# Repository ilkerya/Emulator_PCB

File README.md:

Emulator Hardware
Designed in Kicad 9

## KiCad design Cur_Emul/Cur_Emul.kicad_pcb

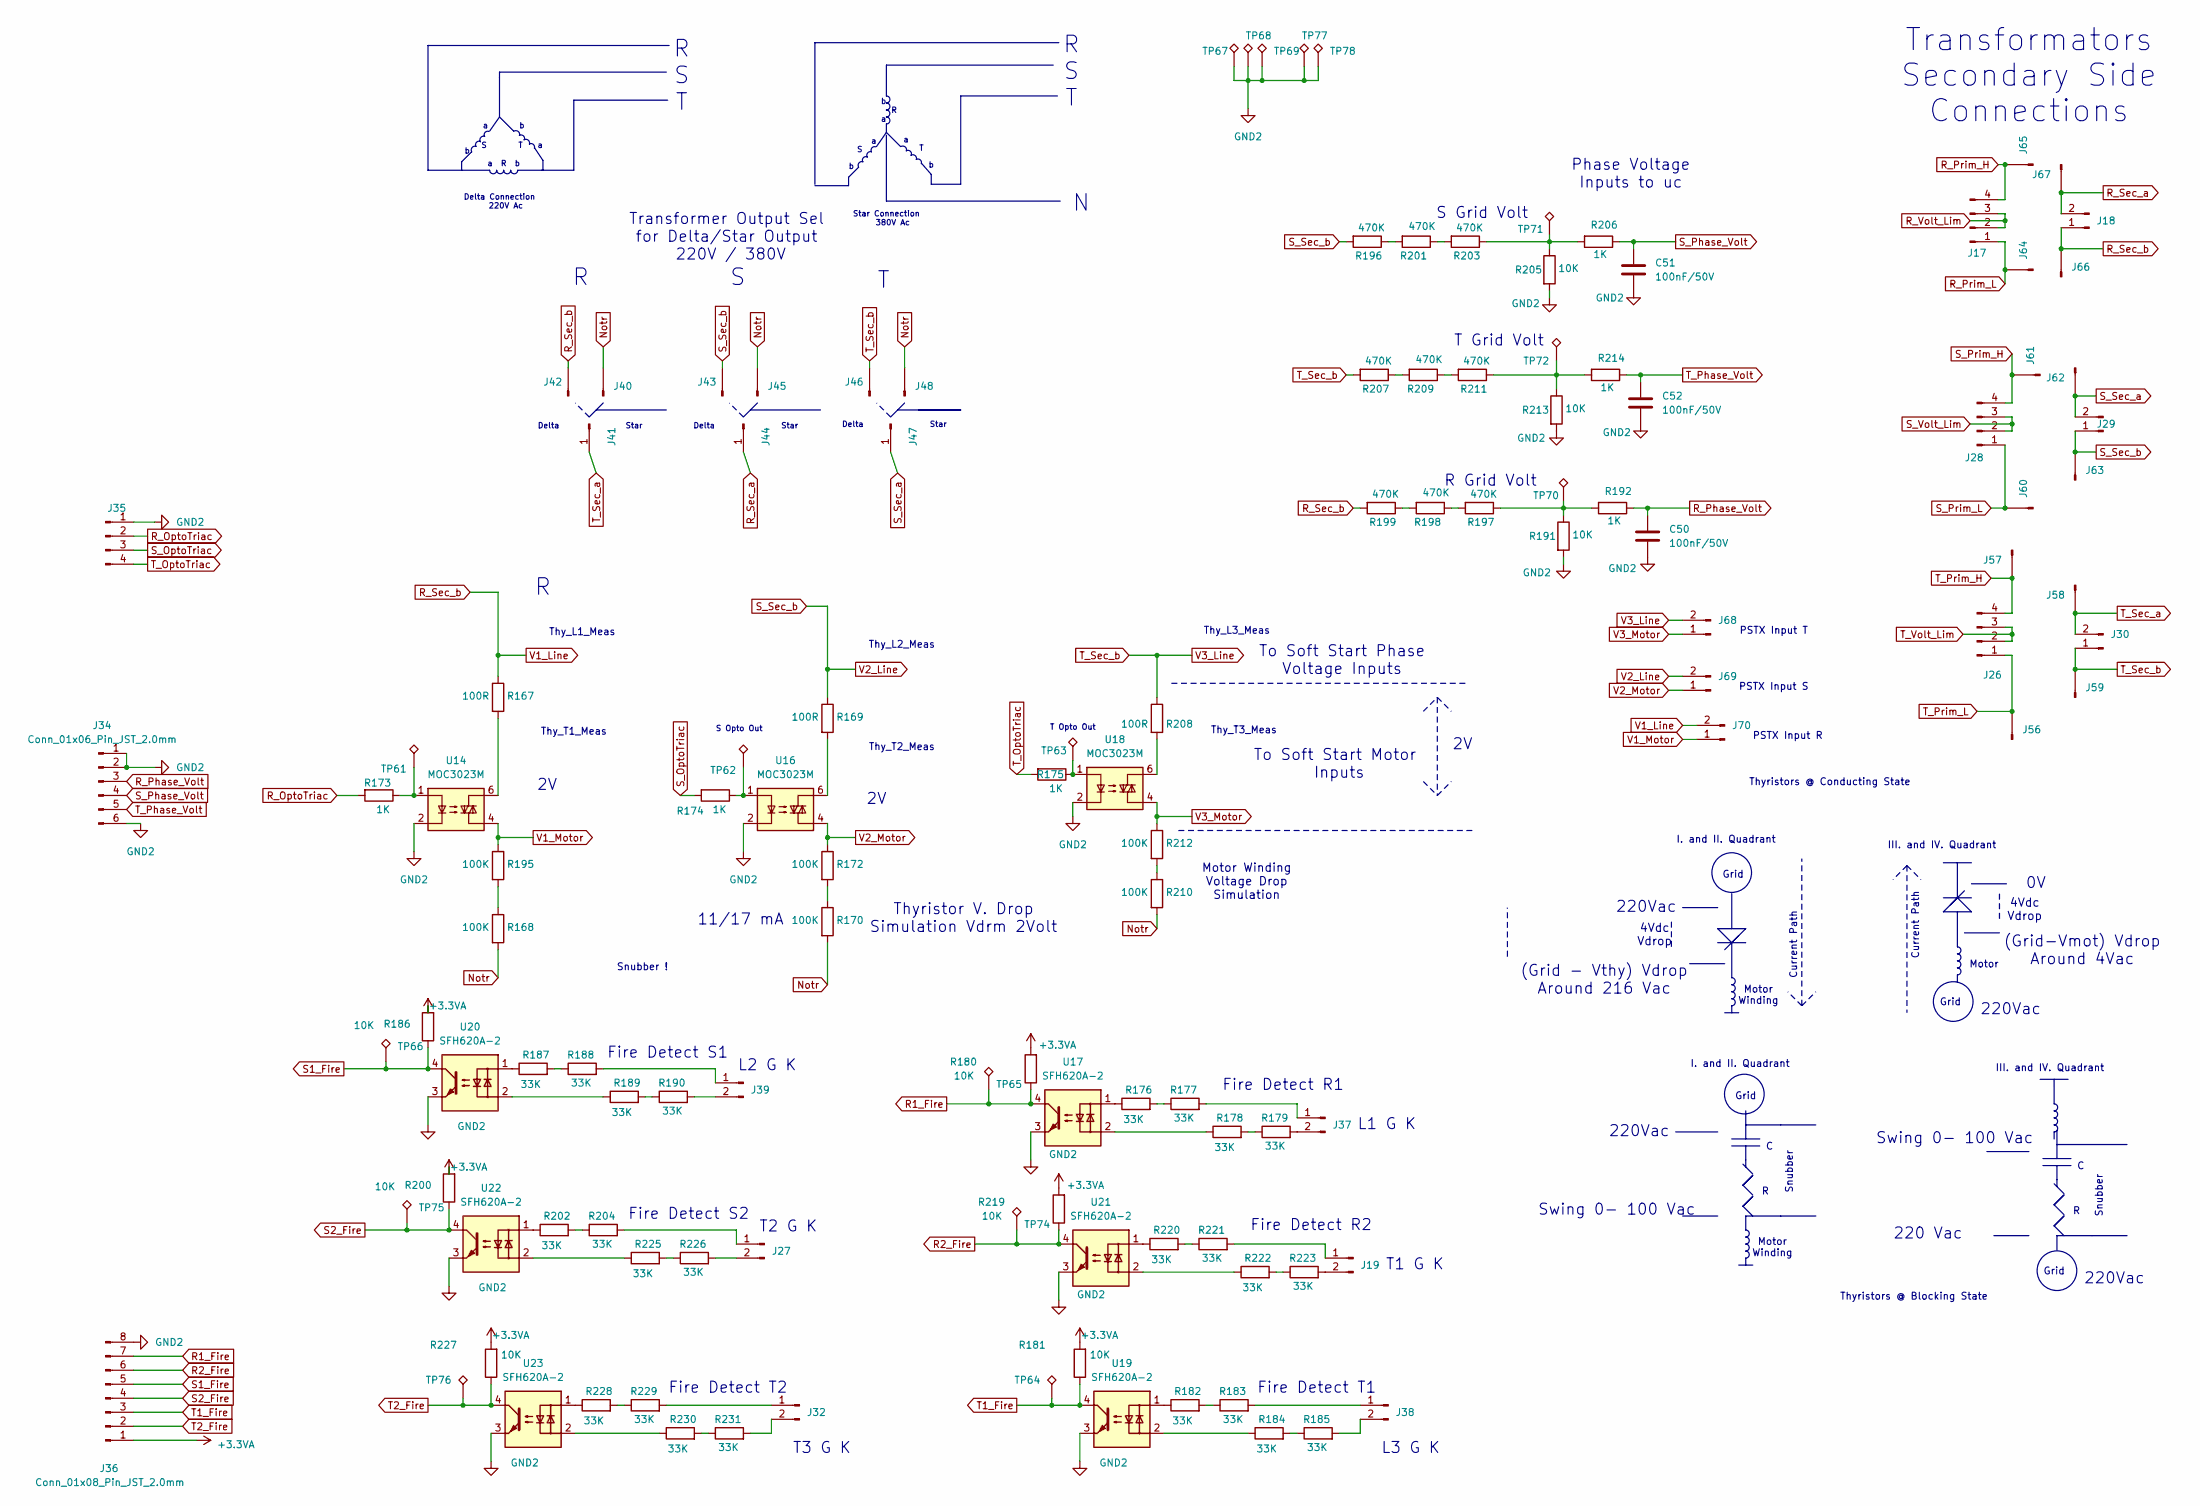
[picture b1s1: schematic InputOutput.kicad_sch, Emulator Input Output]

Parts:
C50, C51, C52: 100nF/50V; C_Rect_L7.0mm_W2.0mm_P5.00mm
J17, J26, J28: Conn_01x04_Pin_JST_2.5mm; JST_EH_B4B-EH-A_1x04_P2.50mm_Vertical
J18, J29, J30, J68, J69, J70: 2x7.50mm_Vertical_PhoenixContact_GMSTB; PhoenixContact_GMSTBVA_2,5_2-G_1x02_P7.50mm_Vertical
J19, J27, J32, J37, J38, J39: 2x7.50mm_Horizontal_PhoenixContact_GMSTBA; PhoenixContact_GMSTBA_2,5_2-G_1x02_P7.50mm_Horizontal
J34: Conn_01x06_Pin_JST_2.0mm; JST_PH_B6B-PH-K_1x06_P2.00mm_Vertical
J35: Conn_01x04_Pin_JST_2.0mm; JST_PH_B4B-PH-K_1x04_P2.00mm_Vertical
J36: Conn_01x08_Pin_JST_2.0mm; JST_PH_B8B-PH-K_1x08_P2.00mm_Vertical
J40, J41, J42, J43, J44, J45, J46, J47, J48, J56, J57, J58, J59, J60, J61, J62, J63, J64, J65, J66, J67: PinHeader_1x2.54mm; PinHeader_1x01_P2.54mm_Vertical
R167, R169, R208: 100R; R_Axial_DIN0207_L6.3mm_D2.5mm_P7.62mm_Horizontal
R168, R170, R172, R195, R210, R212: 100K; R_Axial_DIN0207_L6.3mm_D2.5mm_P7.62mm_Horizontal
R173, R174, R175, R192, R206, R214: 1K; R_Axial_DIN0207_L6.3mm_D2.5mm_P7.62mm_Horizontal
R176, R177, R178, R179, R182, R183, R184, R185, R187, R188, R189, R190, R202, R204, R220, R221, R222, R223, R225, R226, R228, R229, R230, R231: 33K; R_Axial_DIN0207_L6.3mm_D2.5mm_P7.62mm_Horizontal
R180, R181, R186, R191, R200, R205, R213, R219, R227: 10K; R_Axial_DIN0207_L6.3mm_D2.5mm_P7.62mm_Horizontal
R196, R197, R198, R199, R201, R203, R207, R209, R211: 470K; R_Axial_DIN0207_L6.3mm_D2.5mm_P7.62mm_Horizontal
TP61, TP62, TP63, TP64, TP65, TP66, TP67, TP68, TP69, TP70, TP71, TP72, TP74, TP75, TP76, TP77, TP78: Test_Point_THT_KeyStone; TestPoint_Loop_D1.80mm_Drill1.0mm_Beaded
U14, U16, U18: MOC3023M; DIP-6_W7.62mm
U17, U19, U20, U21, U22, U23: SFH620A-2; DIP-4_W7.62mm

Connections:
+3.3VA: J36.1, R180.2, R181.2, R186.2, R200.2, R219.2, R227.2; also elsewhere on the board
GND2: C50.2, C51.2, C52.2, J34.1, J34.2, J34.6, J35.1, J36.8, R191.2, R205.2, R213.2, TP67.1, TP68.1, TP69.1, TP77.1, TP78.1, U14.2, U16.2, U17.3, U18.2, U19.3, U20.3, U21.3, U22.3, U23.3; also elsewhere on the board
unnamed: J19.1, R221.2
unnamed: J19.2, R223.2
unnamed: J27.1, R204.2
unnamed: J27.2, R226.2
unnamed: J32.1, R229.2
unnamed: J32.2, R231.2
unnamed: J37.1, R177.2
unnamed: J37.2, R179.2
unnamed: J38.1, R183.2
unnamed: J38.2, R185.2
unnamed: J39.1, R188.2
unnamed: J39.2, R190.2
unnamed: R167.2, U14.6
unnamed: R168.1, R195.2
unnamed: R169.2, U16.6
unnamed: R170.1, R172.2
unnamed: R173.1, TP61.1, U14.1
unnamed: R174.1, TP62.1, U16.1
unnamed: R175.1, TP63.1, U18.1
unnamed: R176.1, U17.1
unnamed: R176.2, R177.1
unnamed: R178.1, U17.2
unnamed: R178.2, R179.1
unnamed: R182.1, U19.1
unnamed: R182.2, R183.1
unnamed: R184.1, U19.2
unnamed: R184.2, R185.1
unnamed: R187.1, U20.1
unnamed: R187.2, R188.1
unnamed: R189.1, U20.2
unnamed: R189.2, R190.1
unnamed: R191.1, R192.2, R197.1, TP70.1
unnamed: R196.1, R201.2
unnamed: R197.2, R198.1
unnamed: R198.2, R199.1
unnamed: R201.1, R203.2
unnamed: R202.1, U22.1
unnamed: R202.2, R204.1
unnamed: R203.1, R205.1, R206.2, TP71.1
unnamed: R207.1, R209.2
unnamed: R208.2, U18.6
unnamed: R209.1, R211.2
unnamed: R210.1, R212.2
unnamed: R211.1, R213.1, R214.2, TP72.1
unnamed: R220.1, U21.1
unnamed: R220.2, R221.1
unnamed: R222.1, U21.2
unnamed: R222.2, R223.1
unnamed: R225.1, U22.2
unnamed: R225.2, R226.1
unnamed: R228.1, U23.1
unnamed: R228.2, R229.1
unnamed: R230.1, U23.2
unnamed: R230.2, R231.1
Notr: J40.1, J45.1, J48.1, R168.2, R170.2, R210.2
R1_Fire: J36.7, R180.1, TP65.1, U17.4
R2_Fire: J36.6, R219.1, TP74.1, U21.4
R_OptoTriac: J35.2, R173.2
R_Phase_Volt: C50.1, J34.3, R192.1
R_Prim_H: J17.4, J65.1; also elsewhere on the board
R_Prim_L: J17.1, J64.1; also elsewhere on the board
R_Sec_a: J18.2, J44.1, J67.1; also elsewhere on the board
R_Sec_b: J18.1, J42.1, J66.1, J70.2, R167.1, R199.2; also elsewhere on the board
R_Volt_Lim: J17.2, J17.3; also elsewhere on the board
S1_Fire: J36.5, R186.1, TP66.1, U20.4
S2_Fire: J36.4, R200.1, TP75.1, U22.4
S_OptoTriac: J35.3, R174.2
S_Phase_Volt: C51.1, J34.4, R206.1
S_Prim_H: J28.4, J61.1; also elsewhere on the board
S_Prim_L: J28.1, J60.1; also elsewhere on the board
S_Sec_a: J29.2, J47.1, J62.1; also elsewhere on the board
S_Sec_b: J29.1, J43.1, J63.1, J69.2, R169.1, R196.2; also elsewhere on the board
S_Volt_Lim: J28.2, J28.3; also elsewhere on the board
T1_Fire: J36.3, R181.1, TP64.1, U19.4
T2_Fire: J36.2, R227.1, TP76.1, U23.4
T_OptoTriac: J35.4, R175.2
T_Phase_Volt: C52.1, J34.5, R214.1
T_Prim_H: J26.4, J57.1; also elsewhere on the board
T_Prim_L: J26.1, J56.1; also elsewhere on the board
T_Sec_a: J30.2, J41.1, J58.1; also elsewhere on the board
T_Sec_b: J30.1, J46.1, J59.1, J68.2, R207.2, R208.1; also elsewhere on the board
T_Volt_Lim: J26.2, J26.3; also elsewhere on the board
V1_Motor: J70.1, R195.1, U14.4
V2_Motor: J69.1, R172.1, U16.4
V3_Motor: J68.1, R212.1, U18.4

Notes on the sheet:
Thy_L3_Meas
Motor Winding
Fire Detect R1
Fire Detect T2
I. and II. Quadrant
Thy_T2_Meas
Transformators Secondary Side Connections
Thy_L1_Meas
Fire Detect S1
4Vdc Vdrop
T2 G K
Phase Voltage Inputs to uc
S Grid Volt
Snubber
S Opto Out
Grid
Delta
11/17 mA
Delta Connection 220V Ac
To Soft Start Phase Voltage Inputs
Thy_T3_Meas
Star
Swing 0- 100 Vac
Current Path
Motor Winding Voltage Drop Simulation
III. and IV. Quadrant
220Vac
a R b
Motor
Thy_L2_Meas
Thyristors @ Conducting State
PSTX Input T
PSTX Input R
L3 G K
Fire Detect R2
L2 G K
Fire Detect T1
Thyristors @ Blocking State
To Soft Start Motor Inputs
L1 G K

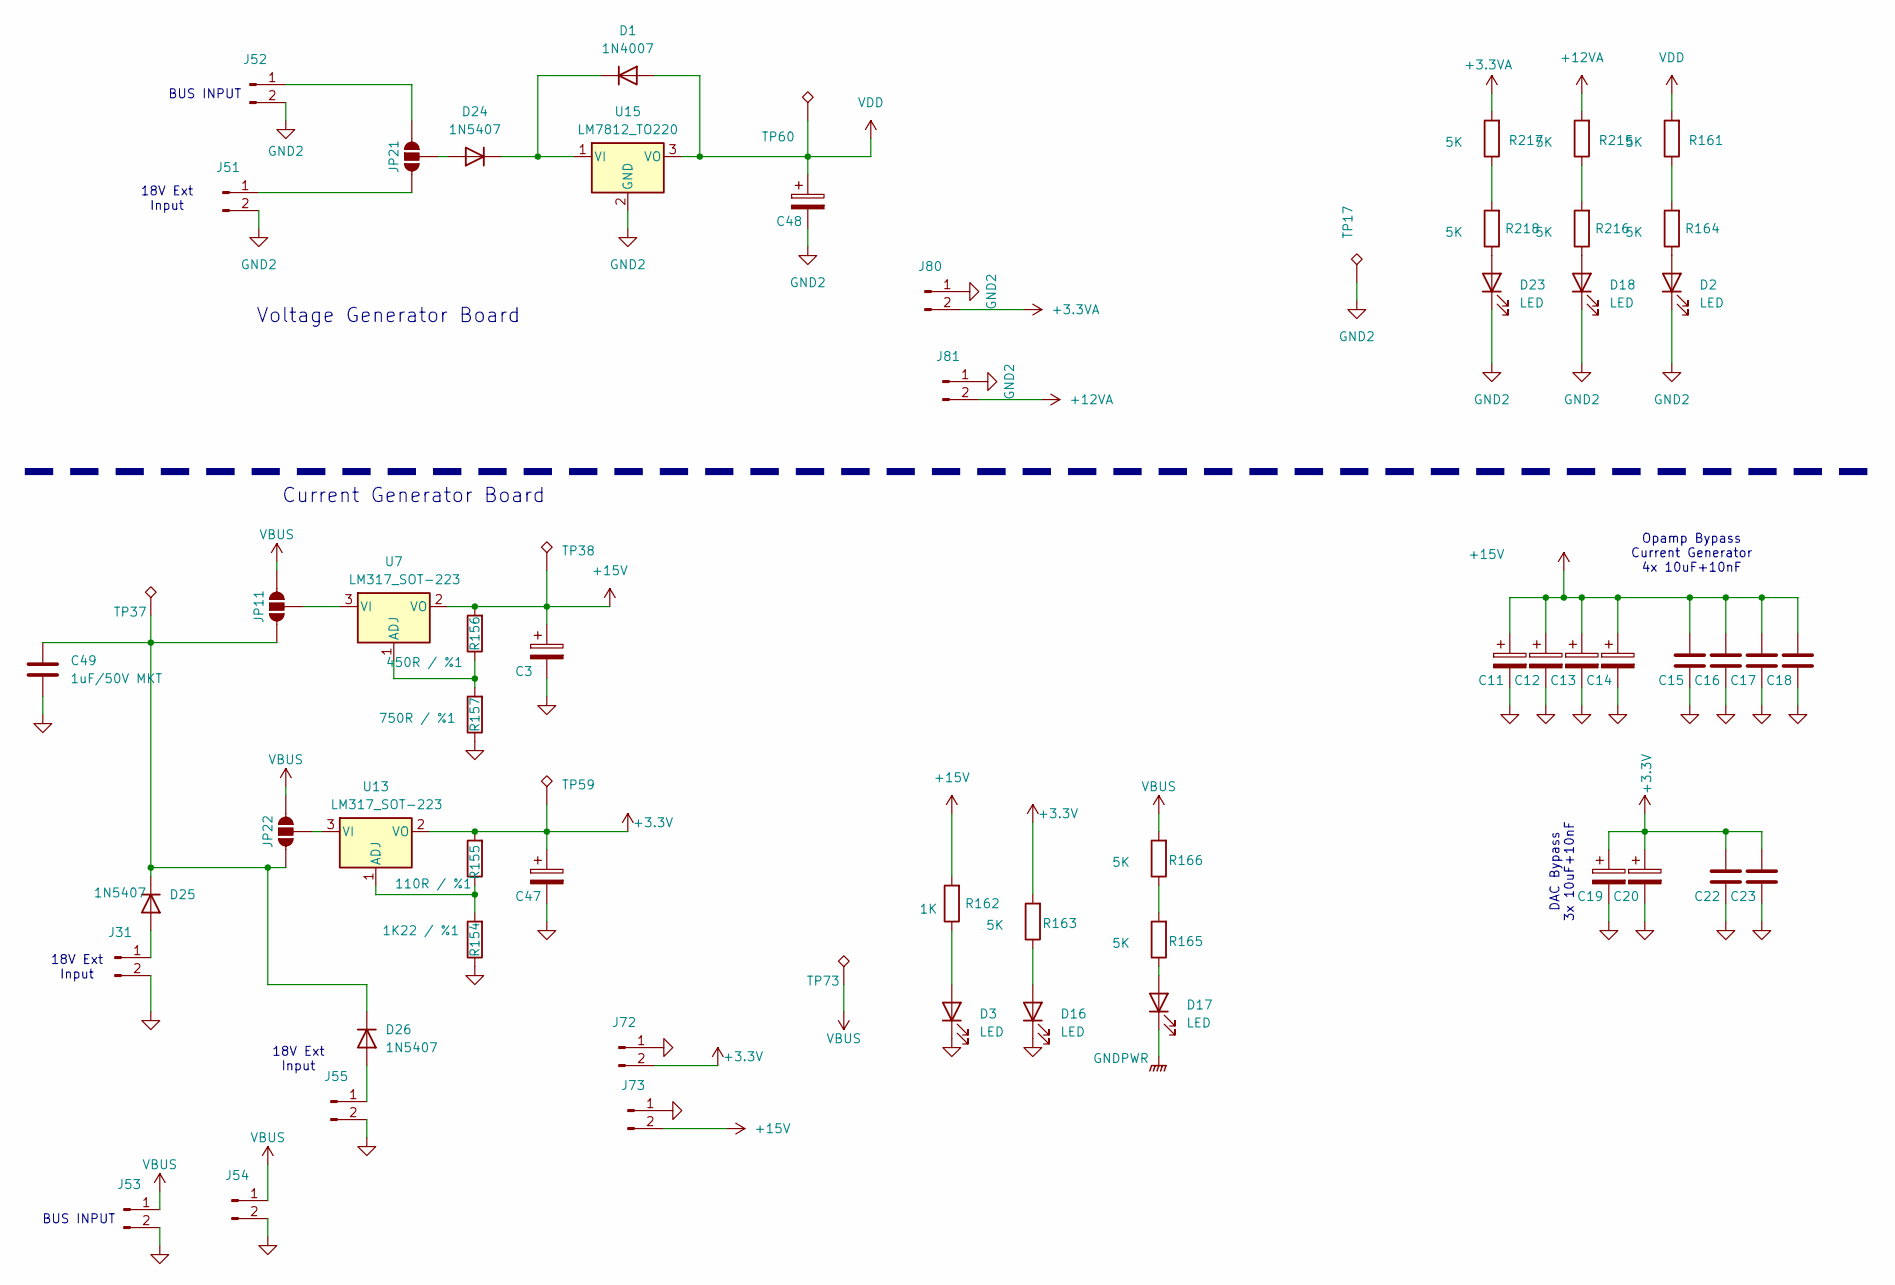
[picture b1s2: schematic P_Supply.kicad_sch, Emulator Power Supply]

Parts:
C3, C47: 100uF/50V; CP_Elec_6.3x7.7
C11, C12, C13, C14, C19, C20: 10uF/50V; CP_Elec_4x3.9
C15, C16, C17, C18, C22, C23: 10nF/50V; C_0805_2012Metric_Pad1.18x1.45mm_HandSolder
C48: 1000uF/50V; CP_Radial_D24.0mm_P10.00mm_SnapIn
C49: 1uF/50V MKT; C_Rect_L28.0mm_W12.0mm_P22.50mm_MKS4
D1: 1N4007; D_DO-41_SOD81_P10.16mm_Horizontal
D2, D3, D16, D17, D18, D23: LED; LED_0805_2012Metric_Pad1.15x1.40mm_HandSolder
D24, D25, D26: 1N5407; D_DO-201AD_P15.24mm_Horizontal
J31, J51, J52, J53, J54, J55, J72, J73, J80, J81: 2x7.50mm_Horizontal_PhoenixContact_GMSTBA; PhoenixContact_GMSTBA_2,5_2-G_1x02_P7.50mm_Horizontal
JP11, JP21, JP22: SolderJumper_3_Open; SolderJumper-3_P2.0mm_Open_TrianglePad1.0x1.5mm
R154: 1K22 / %1; R_0805_2012Metric_Pad1.20x1.40mm_HandSolder
R155: 110R / %1; R_0805_2012Metric_Pad1.20x1.40mm_HandSolder
R156: 450R / %1; R_0805_2012Metric_Pad1.20x1.40mm_HandSolder
R157: 750R / %1; R_0805_2012Metric_Pad1.20x1.40mm_HandSolder
R161, R163, R164, R165, R166, R215, R216, R217, R218: 5K; R_0805_2012Metric_Pad1.20x1.40mm_HandSolder
R162: 1K; R_0805_2012Metric_Pad1.20x1.40mm_HandSolder
TP17, TP37, TP38, TP59, TP60, TP73: Test_Point_THT_KeyStone; TestPoint_Loop_D1.80mm_Drill1.0mm_Beaded
U7, U13: LM317_SOT-223; SOT-223-3_TabPin2
U15: LM7812_TO220; TO-220-3_Vertical

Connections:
+3.3V: C19.1, C20.1, C22.1, C23.1, C47.1, J72.2, R155.2, R163.2, TP59.1, U13.2 (VO); also elsewhere on the board
+3.3VA: J80.2, R217.2; also elsewhere on the board
+12VA: J81.2, R215.2; also elsewhere on the board
+15V: C3.1, C11.1, C12.1, C13.1, C14.1, C15.1, C16.1, C17.1, C18.1, J73.2, R156.2, R162.2, TP38.1, U7.2 (VO); also elsewhere on the board
GND: C3.2, C11.2, C12.2, C13.2, C14.2, C15.2, C16.2, C17.2, C18.2, C19.2, C20.2, C22.2, C23.2, C47.2, C49.2, D3.1 (K), D16.1 (K), J31.2, J53.2, J54.2, J55.2, J72.1, J73.1, R154.1, R157.1; also elsewhere on the board
GND2: C48.2, D2.1 (K), D18.1 (K), D23.1 (K), J51.2, J52.2, J80.1, J81.1, TP17.1, U15.2 (GND); also elsewhere on the board
GNDPWR: D17.1 (K); also elsewhere on the board
unnamed: D1.1 (K), D24.1 (K), U15.1 (VI)
unnamed: D2.2 (A), R164.1
unnamed: D3.2 (A), R162.1
unnamed: D16.2 (A), R163.1
unnamed: D17.2 (A), R165.1
unnamed: D18.2 (A), R216.1
unnamed: D23.2 (A), R218.1
unnamed: D24.2 (A), JP21.2 (C)
unnamed: D25.2 (A), J31.1
unnamed: C49.1, D25.1 (K), D26.1 (K), JP11.1 (A), JP22.1 (A), TP37.1
unnamed: D26.2 (A), J55.1
unnamed: J51.1, JP21.3 (B)
unnamed: J52.1, JP21.1 (A)
unnamed: JP11.2 (C), U7.3 (VI)
unnamed: JP22.2 (C), U13.3 (VI)
unnamed: R161.1, R164.2
unnamed: R165.2, R166.1
unnamed: R215.1, R216.2
unnamed: R217.1, R218.2
unnamed: R156.1, R157.2, U7.1 (ADJ)
unnamed: R154.2, R155.1, U13.1 (ADJ)
VBUS: J53.1, J54.1, JP11.3 (B), JP22.3 (B), R166.2, TP73.1; also elsewhere on the board
VDD: C48.1, D1.2 (A), R161.2, TP60.1, U15.3 (VO); also elsewhere on the board

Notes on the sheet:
DAC Bypass 3x 10uF+10nF
Current Generator Board
BUS INPUT
Opamp Bypass Current Generator 4x 10uF+10nF
18V Ext Input
Voltage Generator Board

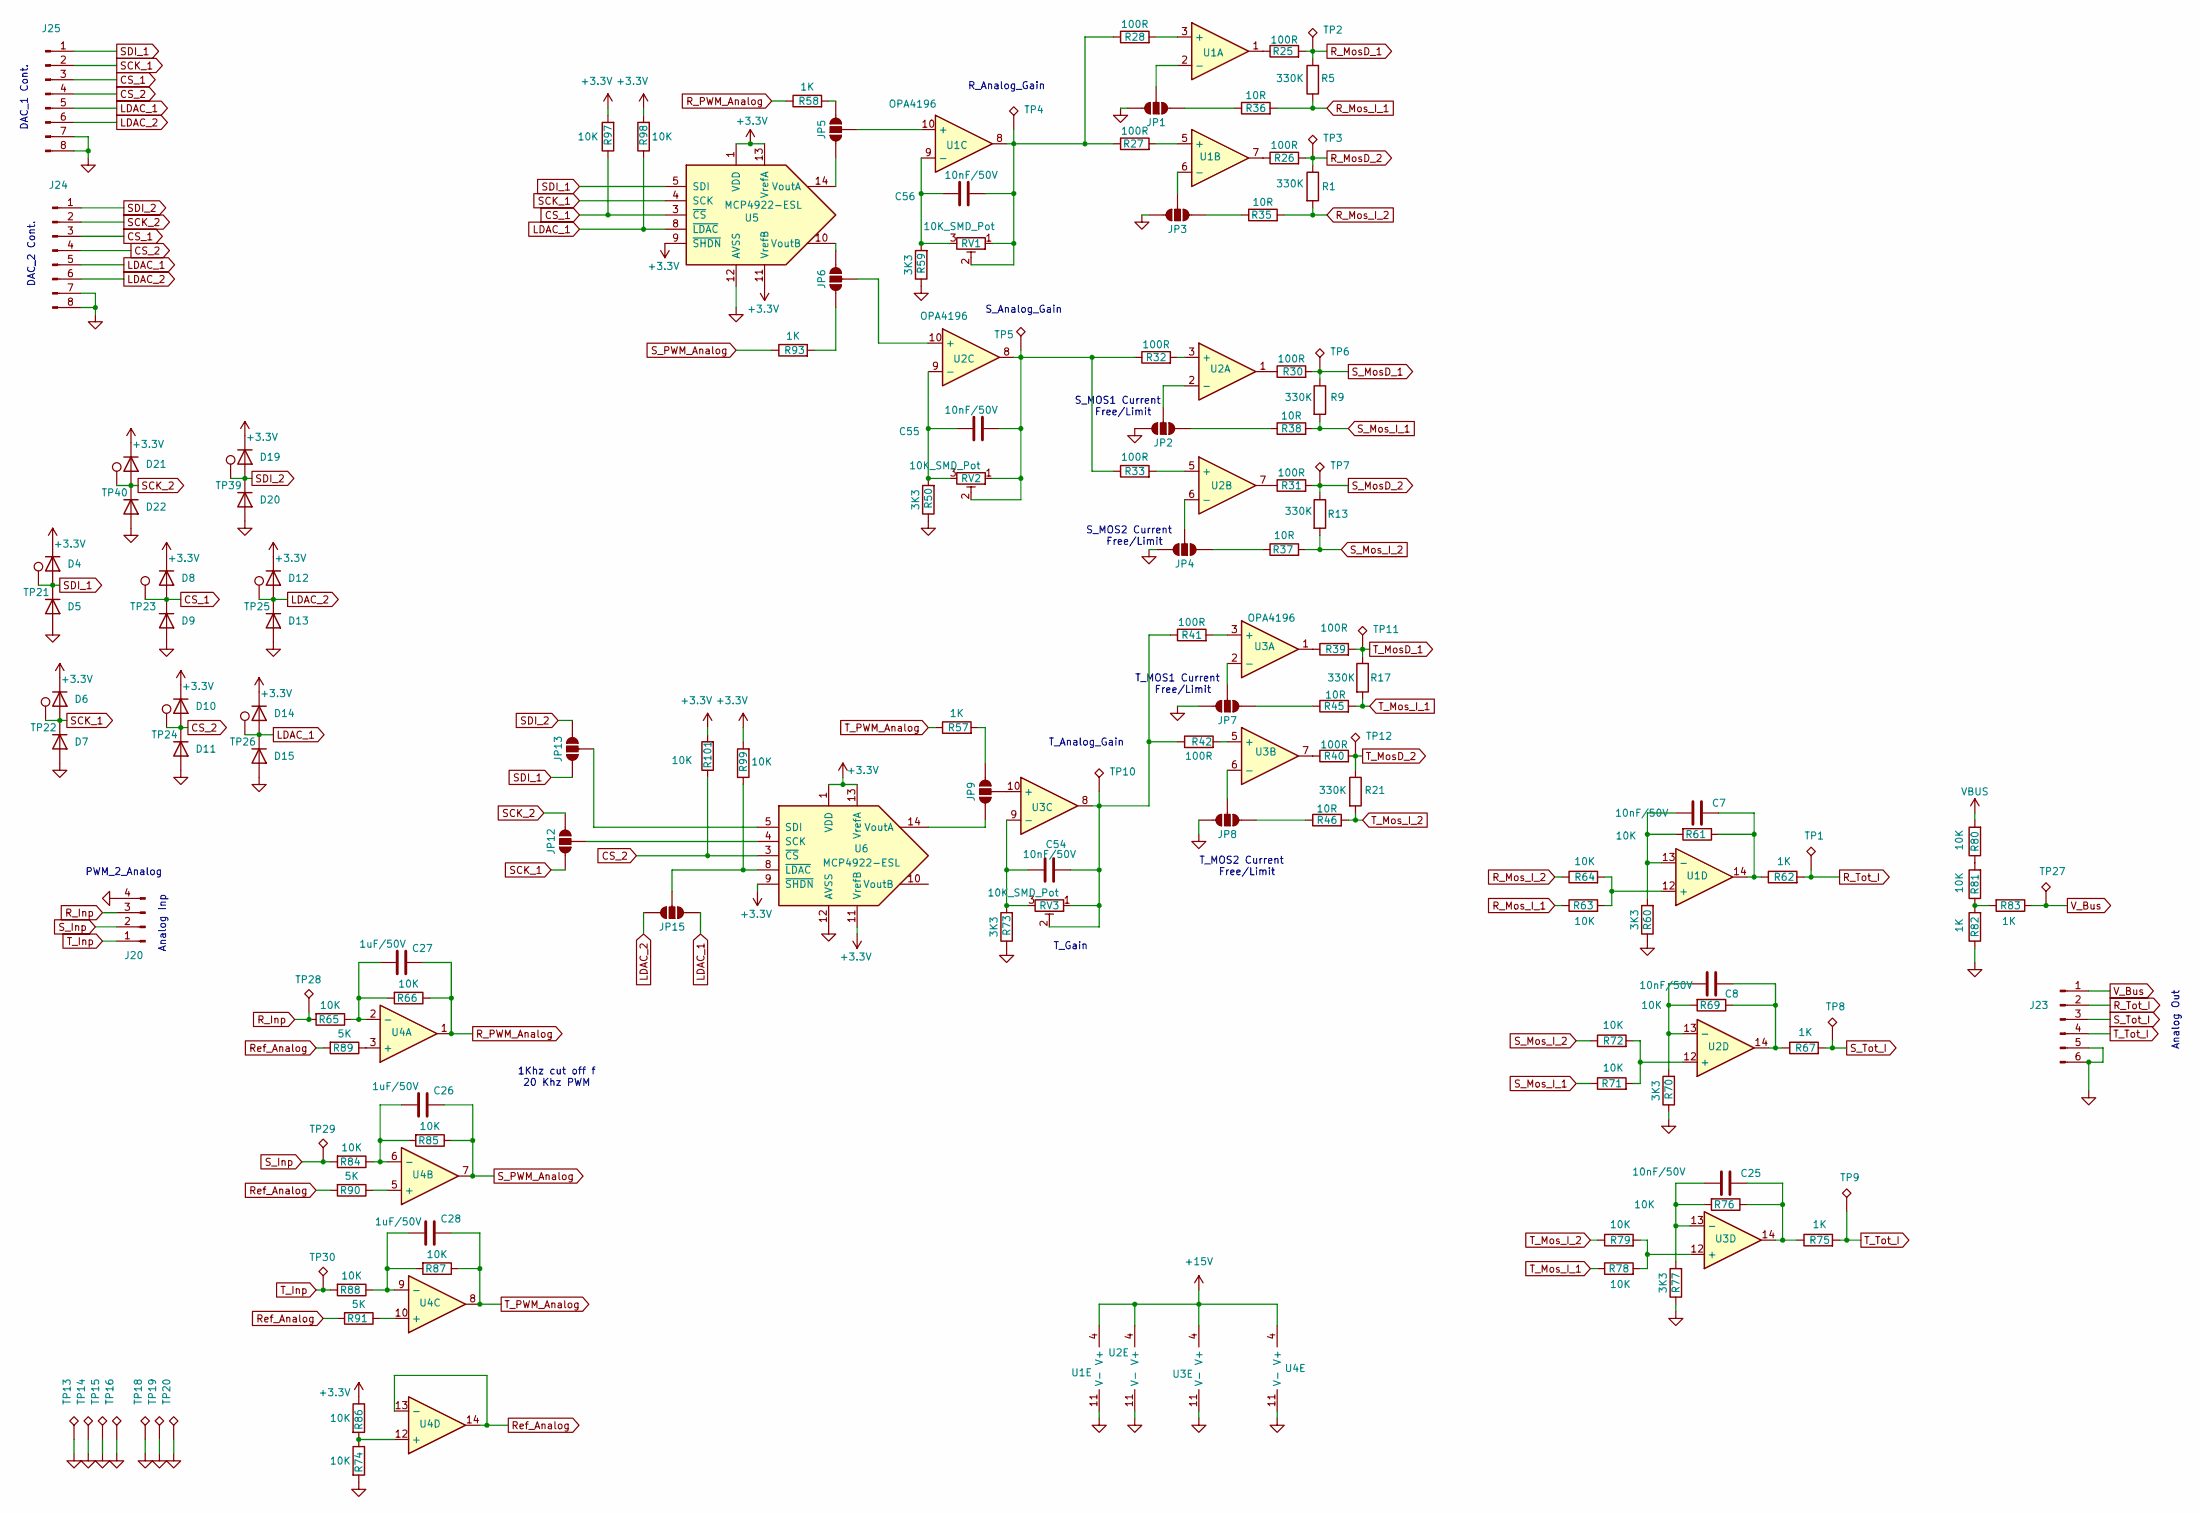
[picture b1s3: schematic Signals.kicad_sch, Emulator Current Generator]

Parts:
C7, C8, C25, C54, C55, C56: 10nF/50V; C_0805_2012Metric_Pad1.18x1.45mm_HandSolder
C26, C27, C28: 1uF/50V; C_1206_3216Metric_Pad1.33x1.80mm_HandSolder
D4, D5, D6, D7, D8, D9, D10, D11, D12, D13, D14, D15, D19, D20, D21, D22: US2AA; D_SMA
J20: Conn_01x04_Pin_JST_2.0mm; JST_PH_B4B-PH-K_1x04_P2.00mm_Vertical
J23: Conn_01x06_Pin_JST_2.0mm; JST_PH_B6B-PH-K_1x06_P2.00mm_Vertical
J24, J25: Conn_01x08_Pin_JST_2.0mm; JST_PH_B8B-PH-K_1x08_P2.00mm_Vertical
JP1, JP2, JP3, JP4, JP5, JP6, JP7, JP8, JP9, JP12, JP13, JP15: SolderJumper_3_Open; SolderJumper-3_P2.0mm_Open_TrianglePad1.0x1.5mm
R1, R5, R9, R13, R17, R21: 330K; R_Axial_DIN0207_L6.3mm_D2.5mm_P7.62mm_Horizontal
R25, R26, R27, R28, R30, R31, R32, R33, R39, R40, R41, R42: 100R; R_0805_2012Metric_Pad1.20x1.40mm_HandSolder
R35, R36, R37, R38, R45, R46: 10R; R_0805_2012Metric_Pad1.20x1.40mm_HandSolder
R50, R59, R60, R70, R73, R77: 3K3; R_0805_2012Metric_Pad1.20x1.40mm_HandSolder
R57, R58, R62, R67, R75, R82, R83, R93: 1K; R_0805_2012Metric_Pad1.20x1.40mm_HandSolder
R61, R63, R64, R65, R66, R69, R71, R72, R74, R76, R78, R79, R80, R81, R84, R85, R86, R87, R88, R97, R98, R99, R101: 10K; R_0805_2012Metric_Pad1.20x1.40mm_HandSolder
R89, R90, R91: 5K; R_0805_2012Metric_Pad1.20x1.40mm_HandSolder
RV1, RV2, RV3: 10K_SMD_Pot; Potentiometer_Bourns_3314J_Vertical
TP1, TP2, TP3, TP4, TP5, TP6, TP7, TP8, TP9, TP10, TP11, TP12, TP13, TP14, TP15, TP16, TP18, TP19, TP20, TP27, TP28, TP29, TP30: Test_Point_THT_KeyStone; TestPoint_Loop_D1.80mm_Drill1.0mm_Beaded
TP21, TP22, TP23, TP24, TP25, TP26, TP39, TP40: Test_Pad_Not_A_Component; TestPoint_Pad_D1.0mm
U1, U2, U3, U4: Opamp_Quad_OPA_4196; SOIC-14_3.9x8.7mm_P1.27mm
U5, U6: MCP4922-ESL; SOIC-14_3.9x8.7mm_P1.27mm

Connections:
+3.3V: D4.1 (K), D6.1 (K), D8.1 (K), D10.1 (K), D12.1 (K), D14.1 (K), D19.1 (K), D21.1 (K), R86.1, R97.2, R98.2, R99.2, R101.2, U5.1 (VDD), U5.9 (~SHDN), U5.11 (VrefB), U5.13 (VrefA), U6.1 (VDD), U6.9 (~SHDN), U6.11 (VrefB), U6.13 (VrefA); also elsewhere on the board
+15V: U1.4 (V+), U2.4 (V+), U3.4 (V+), U4.4 (V+); also elsewhere on the board
CS_1: D8.2 (A), D9.1 (K), J24.3, J25.3, R97.1, TP23.1, U5.3 (~CS)
CS_2: D10.2 (A), D11.1 (K), J24.4, J25.4, R101.1, TP24.1, U6.3 (~CS)
GND: D5.2 (A), D7.2 (A), D9.2 (A), D11.2 (A), D13.2 (A), D15.2 (A), D20.2 (A), D22.2 (A), J20.4, J23.5, J23.6, J24.7, J24.8, J25.7, J25.8, JP1.3 (B), JP2.3 (B), JP3.3 (B), JP4.3 (B), JP7.3 (B), JP8.3 (B), R50.1, R59.1, R60.1, R70.1, R73.1, R74.2, R77.1, R82.1, TP13.1, TP14.1, TP15.1, TP16.1, TP18.1, TP19.1, TP20.1, U1.11 (V-), U2.11 (V-), U3.11 (V-), U4.11 (V-), U5.12 (AVSS), U6.12 (AVSS); also elsewhere on the board
LDAC_1: D14.2 (A), D15.1 (K), J24.5, J25.5, JP15.1 (A), R98.1, TP26.1, U5.8 (~LDAC)
LDAC_2: D12.2 (A), D13.1 (K), J24.6, J25.6, JP15.3 (B), TP25.1
unnamed: C7.2, R61.1, R62.1, U1.14
unnamed: C8.2, R67.1, R69.1, U2.14
unnamed: C25.2, R75.1, R76.1, U3.14
unnamed: C54.2, R41.1, R42.1, RV3.1, RV3.2, TP10.1, U3.8
unnamed: C55.2, R32.1, R33.1, RV2.1, RV2.2, TP5.1, U2.8
unnamed: C56.2, R27.1, R28.1, RV1.1, RV1.2, TP4.1, U1.8
unnamed: JP1.1 (A), R36.1
unnamed: JP1.2 (C), U1.2 (-)
unnamed: JP2.1 (A), R38.1
unnamed: JP2.2 (C), U2.2 (-)
unnamed: JP3.1 (A), R35.1
unnamed: JP3.2 (C), U1.6 (-)
unnamed: JP4.1 (A), R37.1
unnamed: JP4.2 (C), U2.6 (-)
unnamed: JP5.1 (A), U5.14 (VoutA)
unnamed: JP5.3 (B), R58.2
unnamed: JP5.2 (C), U1.10 (+)
unnamed: JP6.1 (A), R93.2
unnamed: JP6.3 (B), U5.10 (VoutB)
unnamed: JP6.2 (C), U2.10 (+)
unnamed: JP7.1 (A), R45.1
unnamed: JP7.2 (C), U3.2 (-)
unnamed: JP8.1 (A), R46.1
unnamed: JP8.2 (C), U3.6 (-)
unnamed: JP9.1 (A), U6.14 (VoutA)
unnamed: JP9.3 (B), R57.2
unnamed: JP9.2 (C), U3.10 (+)
unnamed: JP12.2 (C), U6.4 (SCK)
unnamed: JP13.2 (C), U6.5 (SDI)
unnamed: JP15.2 (C), R99.1, U6.8 (~LDAC)
unnamed: R25.1, U1.1
unnamed: R26.1, U1.7
unnamed: R30.1, U2.1
unnamed: R31.1, U2.7
unnamed: R39.1, U3.1
unnamed: R40.1, U3.7
unnamed: R80.1, R81.2
unnamed: R81.1, R82.2, R83.2
unnamed: R28.2, U1.3 (+)
unnamed: R27.2, U1.5 (+)
unnamed: C56.1, R59.2, RV1.3, U1.9 (-)
unnamed: R63.2, R64.2, U1.12 (+)
unnamed: C7.1, R60.2, R61.2, U1.13 (-)
unnamed: R32.2, U2.3 (+)
unnamed: R33.2, U2.5 (+)
unnamed: C55.1, R50.2, RV2.3, U2.9 (-)
unnamed: R71.2, R72.2, U2.12 (+)
unnamed: C8.1, R69.2, R70.2, U2.13 (-)
unnamed: R41.2, U3.3 (+)
unnamed: R42.2, U3.5 (+)
unnamed: C54.1, R73.2, RV3.3, U3.9 (-)
unnamed: R78.2, R79.2, U3.12 (+)
unnamed: C25.1, R76.2, R77.2, U3.13 (-)
unnamed: R89.1, U4.3 (+)
unnamed: C27.1, R65.1, R66.2, U4.2 (-)
unnamed: R90.1, U4.5 (+)
unnamed: C26.1, R84.1, R85.2, U4.6 (-)
unnamed: R91.1, U4.10 (+)
unnamed: C28.1, R87.2, R88.1, U4.9 (-)
unnamed: R74.1, R86.2, U4.12 (+)
R_Inp: J20.3, R65.2, TP28.1
R_MosD_1: R5.2, R25.2, TP2.1; also elsewhere on the board
R_MosD_2: R1.1, R26.2, TP3.1; also elsewhere on the board
R_Mos_I_1: R5.1, R36.2, R63.1; also elsewhere on the board
R_Mos_I_2: R1.2, R35.2, R64.1; also elsewhere on the board
R_PWM_Analog: C27.2, R58.1, R66.1, U4.1
R_Tot_I: J23.2, R62.2, TP1.1
Ref_Analog: R89.2, R90.2, R91.2, U4.13 (-), U4.14
SCK_1: D6.2 (A), D7.1 (K), J25.2, JP12.1 (A), TP22.1, U5.4 (SCK)
SCK_2: D21.2 (A), D22.1 (K), J24.2, JP12.3 (B), TP40.1
SDI_1: D4.2 (A), D5.1 (K), J25.1, JP13.1 (A), TP21.1, U5.5 (SDI)
SDI_2: D19.2 (A), D20.1 (K), J24.1, JP13.3 (B), TP39.1
S_Inp: J20.2, R84.2, TP29.1
S_MosD_1: R9.1, R30.2, TP6.1; also elsewhere on the board
S_MosD_2: R13.1, R31.2, TP7.1; also elsewhere on the board
S_Mos_I_1: R9.2, R38.2, R71.1; also elsewhere on the board
S_Mos_I_2: R13.2, R37.2, R72.1; also elsewhere on the board
S_PWM_Analog: C26.2, R85.1, R93.1, U4.7
S_Tot_I: J23.3, R67.2, TP8.1
T_Inp: J20.1, R88.2, TP30.1
T_MosD_1: R17.1, R39.2, TP11.1; also elsewhere on the board
T_MosD_2: R21.1, R40.2, TP12.1; also elsewhere on the board
T_Mos_I_1: R17.2, R45.2, R78.1; also elsewhere on the board
T_Mos_I_2: R21.2, R46.2, R79.1; also elsewhere on the board
T_PWM_Analog: C28.2, R57.1, R87.1, U4.8
T_Tot_I: J23.4, R75.2, TP9.1
VBUS: R80.2; also elsewhere on the board
V_Bus: J23.1, R83.1, TP27.1

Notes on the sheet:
S_MOS1 Current Free/Limit
PWM_2_Analog
Analog Out
1Khz cut off f 20 Khz PWM
R_Analog_Gain
T_MOS1 Current Free/Limit
S_Analog_Gain
T_MOS2 Current Free/Limit
T_Analog_Gain
S_MOS2 Current Free/Limit
DAC_1 Cont.
Analog Inp
T_Gain
DAC_2 Cont.
